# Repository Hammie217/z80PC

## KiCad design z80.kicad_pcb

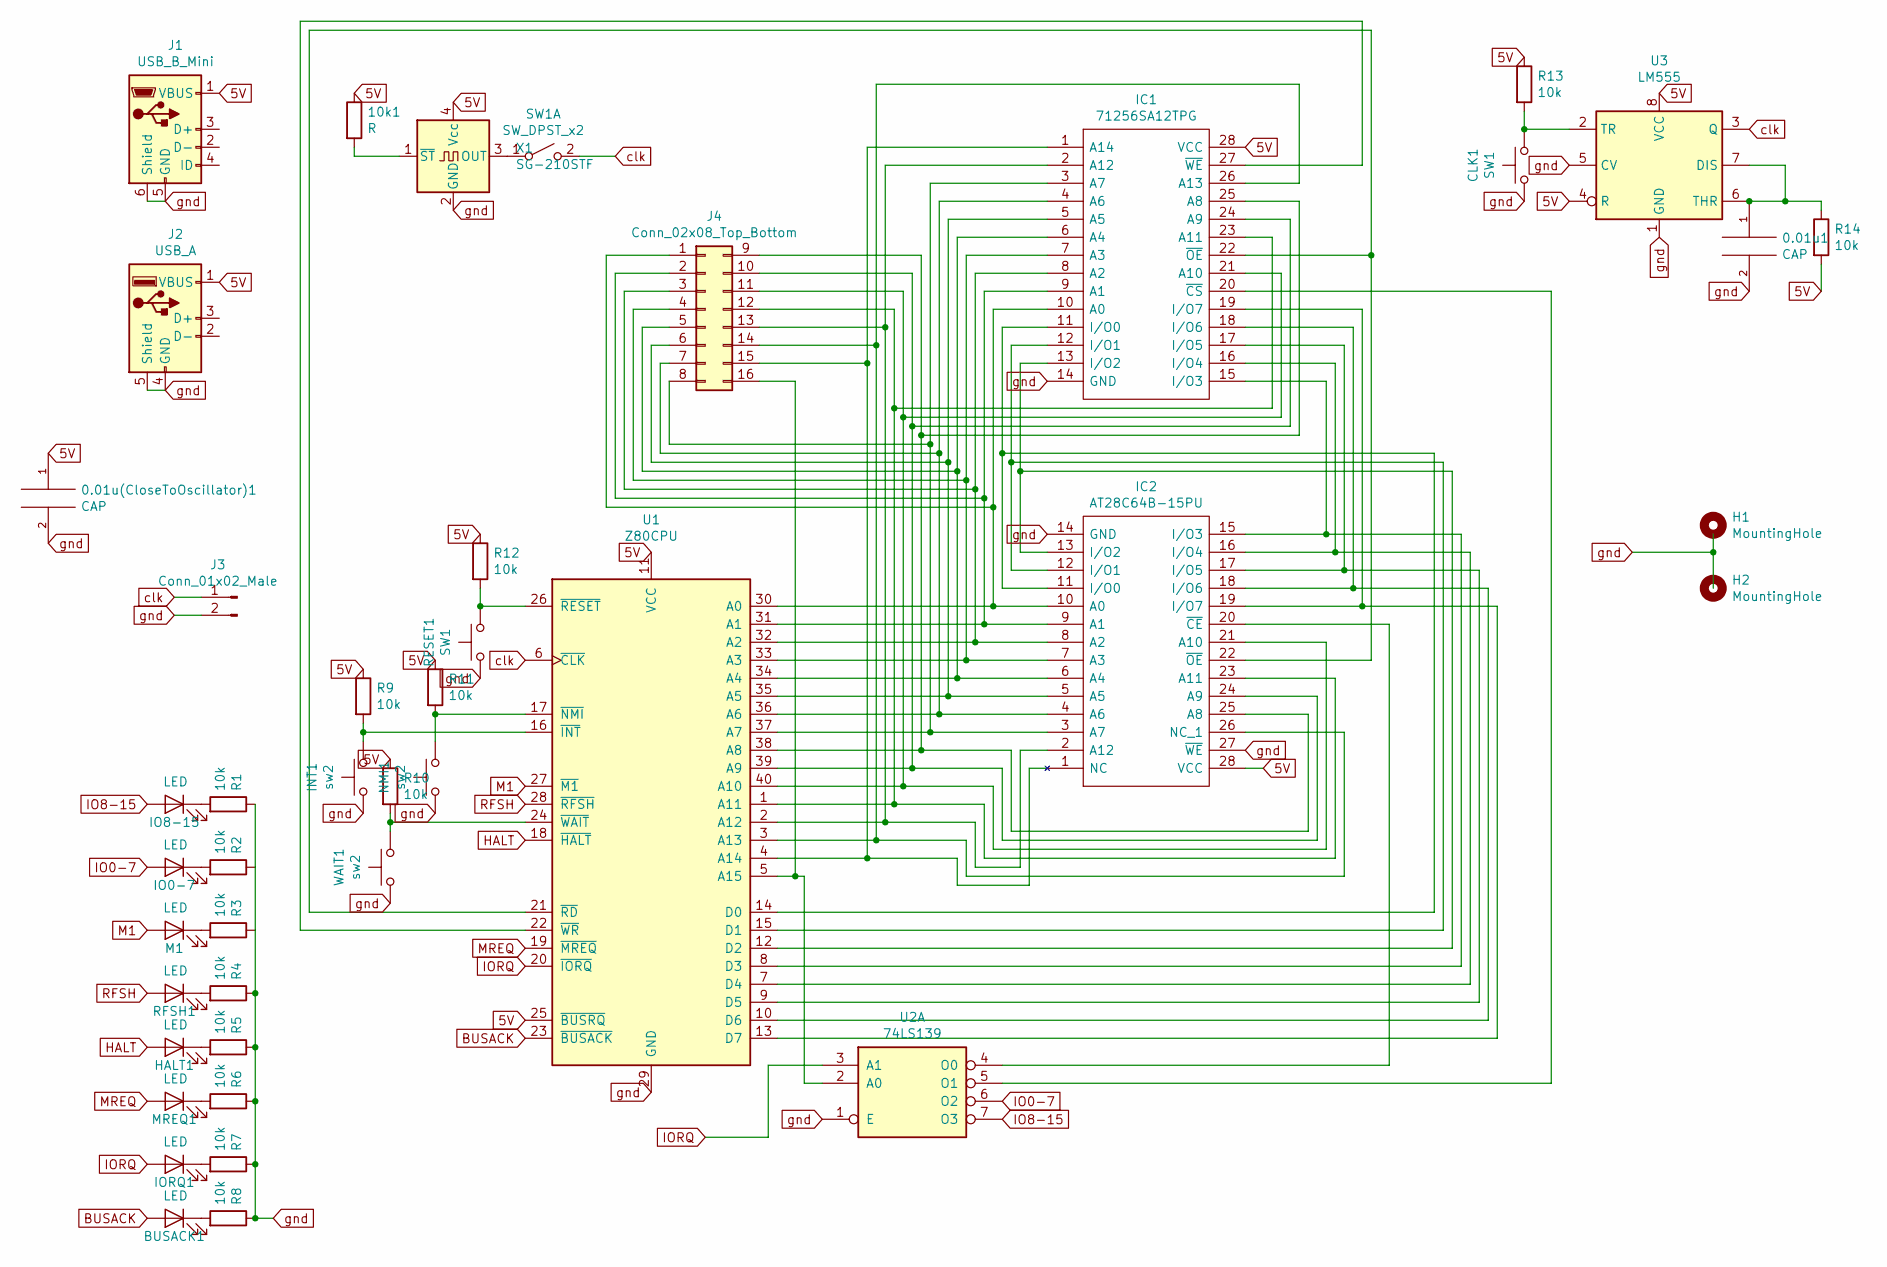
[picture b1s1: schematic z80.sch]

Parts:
0.01u1, 0.01u(CloseToOscillator)1: CAP; C_Disc_D3.0mm_W2.0mm_P2.50mm
10k1: R; R_Axial_DIN0207_L6.3mm_D2.5mm_P10.16mm_Horizontal
BUSACK1: LED; LED_D5.0mm
CLK1: SW1; SW_PUSH_6mm
H1, H2: MountingHole; MountingHole_3.2mm_M3
HALT1: LED; LED_D5.0mm
IC1: 71256SA12TPG; DIP794W56P254L3467H457Q28N; Manufacturer_Part_Number 71256SA12TPG
IC2: AT28C64B-15PU; DIP1556W56P254L3702H483Q28N; Mouser2 Part Number 556-AT28C64B15PU
INT1: sw2; SW_PUSH_6mm
IO0-7, IO8-15: LED; LED_D5.0mm
IORQ1: LED; LED_D5.0mm
J1: USB_B_Mini; USB_Mini-B_Lumberg_2486_01_Horizontal
J2: USB_A; USB_A_CNCTech_1001-011-01101_Horizontal
J3: Conn_01x02_Male; PinHeader_1x02_P2.54mm_Vertical
J4: Conn_02x08_Top_Bottom; PinHeader_2x08_P2.54mm_Vertical
M1: LED; LED_D5.0mm
MREQ1: LED; LED_D5.0mm
NMI1: sw2; SW_PUSH_6mm
R1, R2, R3, R4, R5, R6, R7, R8, R9, R10, R11, R12, R13, R14: 10k; R_Axial_DIN0207_L6.3mm_D2.5mm_P10.16mm_Horizontal
RESET1: SW1; SW_PUSH_6mm
RFSH1: LED; LED_D5.0mm
SW1: SW_DPST_x2; SW_CuK_JS202011CQN_DPDT_Straight
U1: Z80CPU; DIP1550W53P254L5232H508Q40N
U2: 74LS139; DIP-16_W7.62mm_LongPads
U3: LM555; DIP-8_W7.62mm_Socket_LongPads
WAIT1: sw2; SW_PUSH_6mm
X1: SG-210STF; Oscillator_SMD_SeikoEpson_SG210-4Pin_2.5x2.0mm_HandSoldering

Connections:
5V: 0.01u(CloseToOscillator)1.1, 10k1.1, IC1.28 (VCC), IC2.28 (VCC), J1.1 (VBUS), J2.1 (VBUS), R9.1, R10.1, R11.1, R12.1, R13.1, R14.2, U1.11 (VCC), U1.25 (~BUSRQ~), U3.4 (R), U3.8 (VCC), X1.4 (Vcc)
BUSACK: BUSACK1.2 (A), U1.23 (~BUSACK~)
HALT: HALT1.2 (A), U1.18 (~HALT~)
IO0-7: IO0-7.2 (A), U2.6 (O2)
IO8-15: IO8-15.2 (A), U2.7 (O3)
IORQ: IORQ1.2 (A), U1.20 (~IORQ~), U2.3 (A1)
M1: M1.2 (A), U1.27 (~M1~)
MREQ: MREQ1.2 (A), U1.19 (~MREQ~)
unnamed: 0.01u1.1, R14.1, U3.6 (THR), U3.7 (DIS)
unnamed: 10k1.2, X1.1 (~ST~)
unnamed: BUSACK1.1 (K), R8.2
unnamed: CLK1.2, R13.2, U3.2 (TR)
unnamed: HALT1.1 (K), R5.2
unnamed: IC1.1 (A14), IC2.1 (NC), J4.15, U1.4 (A14)
unnamed: IC1.2 (A12), IC2.2 (A12), J4.13, U1.2 (A12)
unnamed: IC1.3 (A7), IC2.3 (A7), J4.8, U1.37 (A7)
unnamed: IC1.4 (A6), IC2.4 (A6), J4.7, U1.36 (A6)
unnamed: IC1.5 (A5), IC2.5 (A5), J4.6, U1.35 (A5)
unnamed: IC1.6 (A4), IC2.6 (A4), J4.5, U1.34 (A4)
unnamed: IC1.7 (A3), IC2.7 (A3), J4.4, U1.33 (A3)
unnamed: IC1.8 (A2), IC2.8 (A2), J4.3, U1.32 (A2)
unnamed: IC1.9 (A1), IC2.9 (A1), J4.2, U1.31 (A1)
unnamed: IC1.10 (A0), IC2.10 (A0), J4.1, U1.30 (A0)
unnamed: IC1.11 (I/O0), IC2.11 (I/O0), U1.14 (D0)
unnamed: IC1.12 (I/O1), IC2.12 (I/O1), U1.15 (D1)
unnamed: IC1.13 (I/O2), IC2.13 (I/O2), U1.12 (D2)
unnamed: IC1.15 (I/O3), IC2.15 (I/O3), U1.8 (D3)
unnamed: IC1.16 (I/O4), IC2.16 (I/O4), U1.7 (D4)
unnamed: IC1.17 (I/O5), IC2.17 (I/O5), U1.9 (D5)
unnamed: IC1.18 (I/O6), IC2.18 (I/O6), U1.10 (D6)
unnamed: IC1.19 (I/O7), IC2.19 (I/O7), U1.13 (D7)
unnamed: IC1.20 (~CS), U2.5 (O1)
unnamed: IC1.21 (A10), IC2.21 (A10), J4.11, U1.40 (A10)
unnamed: IC1.22 (~OE), IC2.22 (~OE), U1.21 (~RD~)
unnamed: IC1.23 (A11), IC2.23 (A11), J4.12, U1.1 (A11)
unnamed: IC1.24 (A9), IC2.24 (A9), J4.10, U1.39 (A9)
unnamed: IC1.25 (A8), IC2.25 (A8), J4.9, U1.38 (A8)
unnamed: IC1.26 (A13), IC2.26 (NC_1), J4.14, U1.3 (A13)
unnamed: IC1.27 (~WE), U1.22 (~WR~)
unnamed: IC2.20 (~CE), U2.4 (O0)
unnamed: INT1.2, R9.2, U1.16 (~INT~)
unnamed: IO0-7.1 (K), R2.2
unnamed: IO8-15.1 (K), R1.2
unnamed: IORQ1.1 (K), R7.2
unnamed: J4.16, U1.5 (A15), U2.2 (A0)
unnamed: M1.1 (K), R3.2
unnamed: MREQ1.1 (K), R6.2
unnamed: NMI1.2, R11.2, U1.17 (~NMI~)
unnamed: R4.2, RFSH1.1 (K)
unnamed: R10.2, U1.24 (~WAIT~), WAIT1.2
unnamed: R12.2, RESET1.2, U1.26 (~RESET~)
unnamed: SW1.1 (A), X1.3 (OUT)
RFSH: RFSH1.2 (A), U1.28 (~RFSH~)
clk: J3.1, SW1.2 (B), U1.6 (~CLK~), U3.3 (Q)
gnd: 0.01u1.2, 0.01u(CloseToOscillator)1.2, CLK1.1, IC1.14 (GND), IC2.14 (GND), IC2.27 (~WE), INT1.1, J1.5 (GND), J1.6 (Shield), J2.4 (GND), J2.5 (Shield), J3.2, NMI1.1, R1.1, R2.1, R3.1, R4.1, R5.1, R6.1, R7.1, R8.1, RESET1.1, U1.29 (GND), U2.1 (E), U3.1 (GND), U3.5 (CV), WAIT1.1, X1.2 (GND)

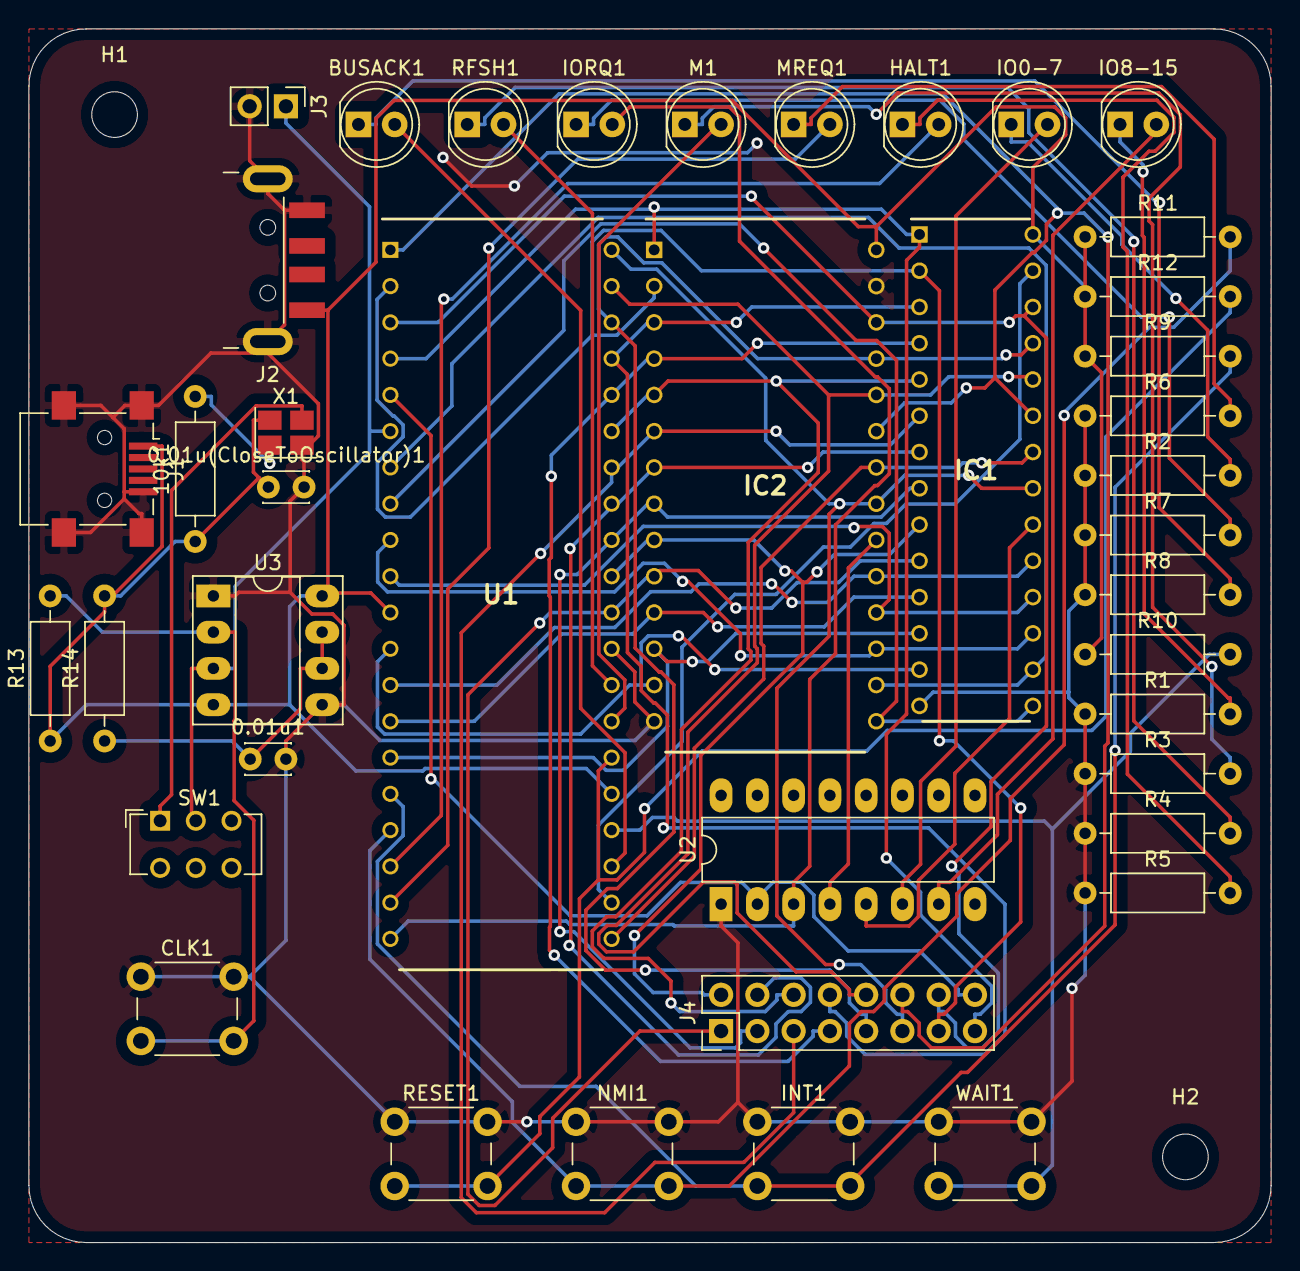
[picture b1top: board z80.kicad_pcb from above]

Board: 2 copper layers, 87.0 x 85.0 mm, 43 parts (0 on the bottom side), 55 nets.

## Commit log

2020-02-04 added PCB
